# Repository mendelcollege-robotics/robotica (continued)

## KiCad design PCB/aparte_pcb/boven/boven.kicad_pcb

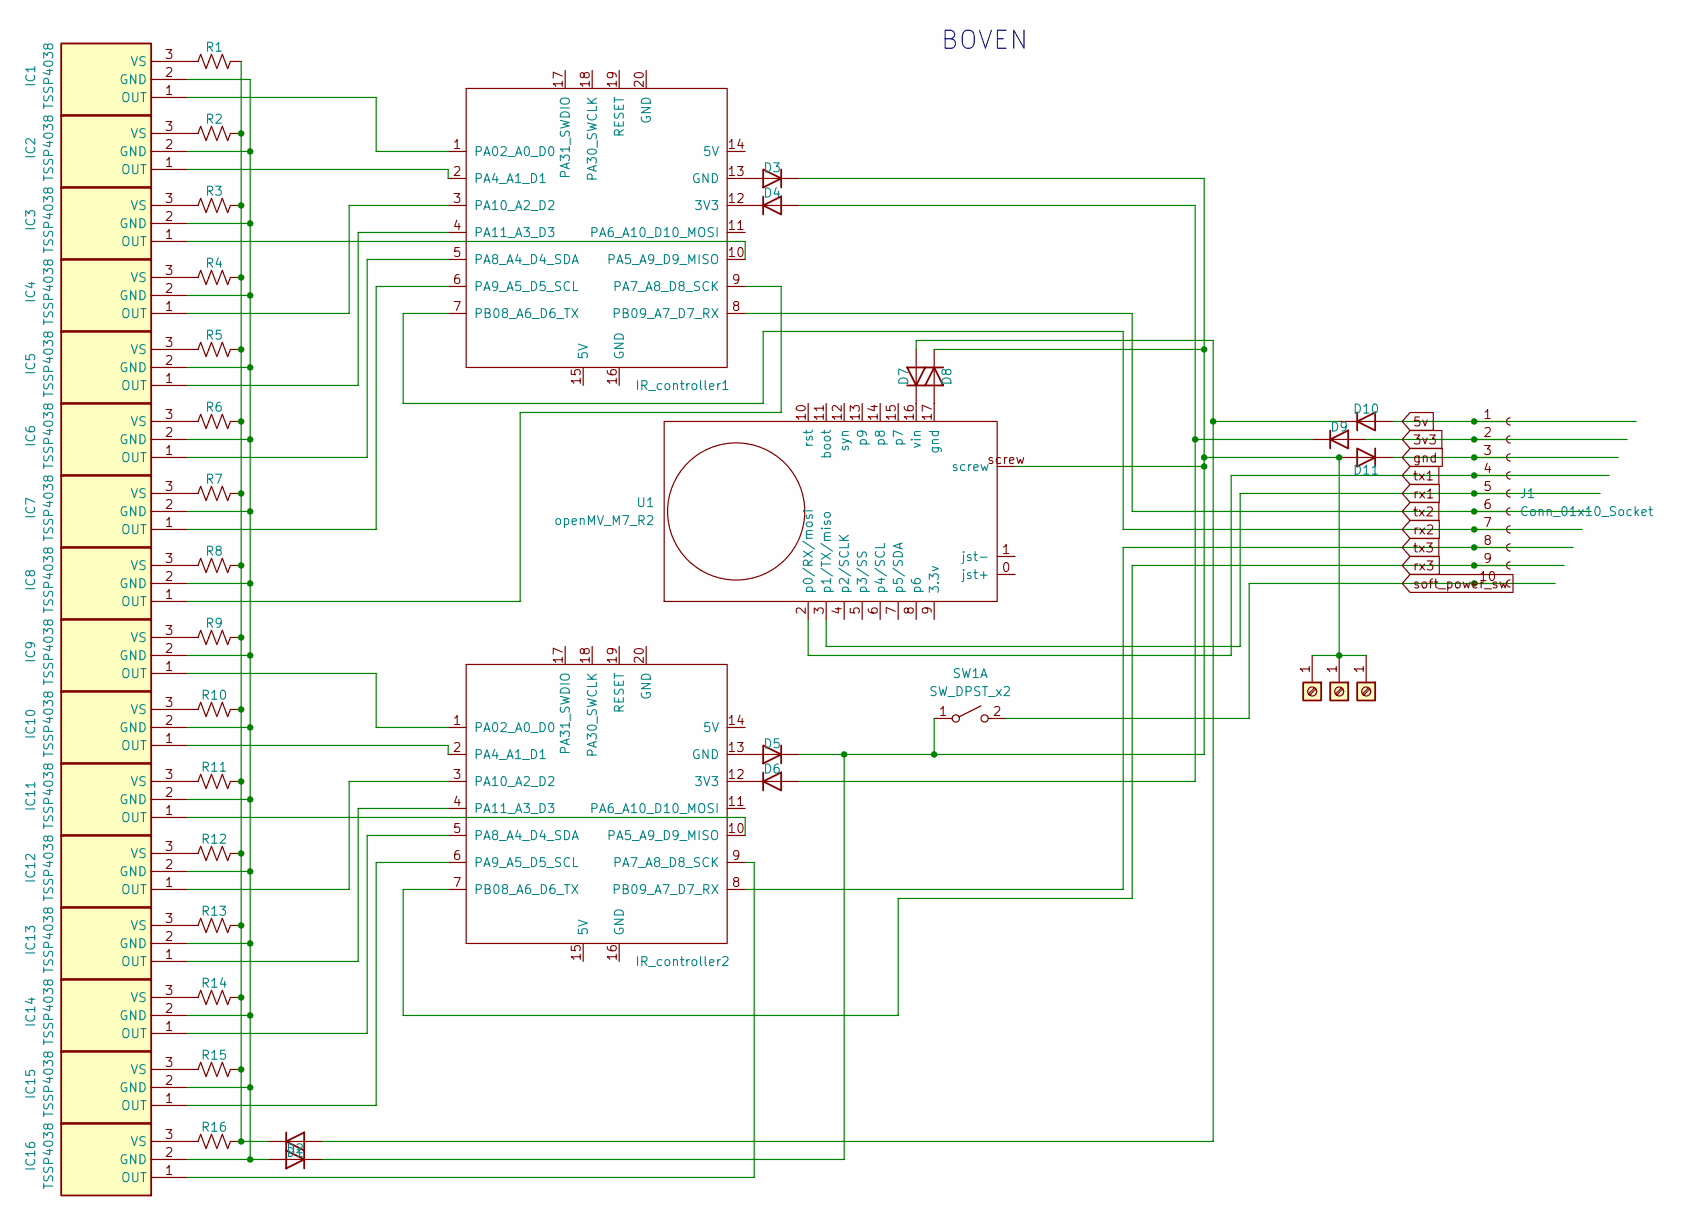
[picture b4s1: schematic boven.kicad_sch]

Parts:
D1, D2, D3, D4, D5, D6, D7, D8, D9, D10, D11: D; D_MELF-RM10_Universal_Handsoldering
IC1, IC2, IC3, IC4, IC5, IC6, IC7, IC8, IC9, IC10, IC11, IC12, IC13, IC14, IC15, IC16: TSSP4038; Manufacturer_Part_Number TSSP4038; Mouser Part Number 782-TSSP4038
IR_controller1, IR_controller2: Seeed Studio XIAO SAMD21; Seeduino Xiao Kicad af
J1: Conn_01x10_Socket; JST_EH_S10B-EH_1x10_P2.50mm_Horizontal
J2: Screw_Terminal_01x01; MountingHole_4.3mm_M4_DIN965_Pad
J3, J4: Screw_Terminal_01x01; MountingHole_4.3mm_M4_ISO7380_Pad
R1, R2, R3, R4, R5, R6, R7, R8, R9, R10, R11, R12, R13, R14, R15, R16: R_US; R_Axial_DIN0207_L6.3mm_D2.5mm_P10.16mm_Horizontal
SW1: SW_DPST_x2; R1966ABLKBLKEF
U1: openMV_M7_R2; openmv_m7_r2

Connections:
3v3: D9.2 (A), J1.2
5v: D10.2 (A), J1.1
unnamed: D1.2 (A), D7.2 (A), D10.1 (K)
unnamed: D1.1 (K), R1.2, R2.2, R3.2, R4.2, R5.2, R6.2, R7.2, R8.2, R9.2, R10.2, R11.2, R12.2, R13.2, R14.2, R15.2, R16.2
unnamed: D2.2 (A), IC1.2 (GND), IC2.2 (GND), IC3.2 (GND), IC4.2 (GND), IC5.2 (GND), IC6.2 (GND), IC7.2 (GND), IC8.2 (GND), IC9.2 (GND), IC10.2 (GND), IC11.2 (GND), IC12.2 (GND), IC13.2 (GND), IC14.2 (GND), IC15.2 (GND), IC16.2 (GND)
unnamed: D3.2 (A), IR_controller1.13 (GND)
unnamed: D4.2 (A), D6.2 (A), D9.1 (K)
unnamed: D4.1 (K), IR_controller1.12 (3V3)
unnamed: D5.2 (A), IR_controller2.13 (GND)
unnamed: D6.1 (K), IR_controller2.12 (3V3)
unnamed: D7.1 (K), U1.16 (vin)
unnamed: D8.2 (A), U1.17 (gnd)
unnamed: D2.1 (K), D3.1 (K), D5.1 (K), D8.1 (K), D11.2 (A), J2.1, J3.1, J4.1, SW1.1 (A), U1.screw
unnamed: IC1.1 (OUT), IR_controller1.1 (PA02_A0_D0)
unnamed: IC1.3 (VS), R1.1
unnamed: IC2.1 (OUT), IR_controller1.2 (PA4_A1_D1)
unnamed: IC2.3 (VS), R2.1
unnamed: IC3.1 (OUT), IR_controller1.10 (PA5_A9_D9_MISO)
unnamed: IC3.3 (VS), R3.1
unnamed: IC4.1 (OUT), IR_controller1.3 (PA10_A2_D2)
unnamed: IC4.3 (VS), R4.1
unnamed: IC5.1 (OUT), IR_controller1.4 (PA11_A3_D3)
unnamed: IC5.3 (VS), R5.1
unnamed: IC6.1 (OUT), IR_controller1.5 (PA8_A4_D4_SDA)
unnamed: IC6.3 (VS), R6.1
unnamed: IC7.1 (OUT), IR_controller1.6 (PA9_A5_D5_SCL)
unnamed: IC7.3 (VS), R7.1
unnamed: IC8.1 (OUT), IR_controller1.9 (PA7_A8_D8_SCK)
unnamed: IC8.3 (VS), R8.1
unnamed: IC9.1 (OUT), IR_controller2.1 (PA02_A0_D0)
unnamed: IC9.3 (VS), R9.1
unnamed: IC10.1 (OUT), IR_controller2.2 (PA4_A1_D1)
unnamed: IC10.3 (VS), R10.1
unnamed: IC11.1 (OUT), IR_controller2.10 (PA5_A9_D9_MISO)
unnamed: IC11.3 (VS), R11.1
unnamed: IC12.1 (OUT), IR_controller2.3 (PA10_A2_D2)
unnamed: IC12.3 (VS), R12.1
unnamed: IC13.1 (OUT), IR_controller2.4 (PA11_A3_D3)
unnamed: IC13.3 (VS), R13.1
unnamed: IC14.1 (OUT), IR_controller2.5 (PA8_A4_D4_SDA)
unnamed: IC14.3 (VS), R14.1
unnamed: IC15.1 (OUT), IR_controller2.6 (PA9_A5_D5_SCL)
unnamed: IC15.3 (VS), R15.1
unnamed: IC16.1 (OUT), IR_controller2.9 (PA7_A8_D8_SCK)
unnamed: IC16.3 (VS), R16.1
gnd: D11.1 (K), J1.3
rx1: J1.5, U1.3 (p1/TX/miso)
rx2: IR_controller1.7 (PB08_A6_D6_TX), J1.7
rx3: IR_controller2.7 (PB08_A6_D6_TX), J1.9
soft_power_sw: J1.10, SW1.2 (B)
tx1: J1.4, U1.2 (p0/RX/mosi)
tx2: IR_controller1.8 (PB09_A7_D7_RX), J1.6
tx3: IR_controller2.8 (PB09_A7_D7_RX), J1.8

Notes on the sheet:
BOVEN

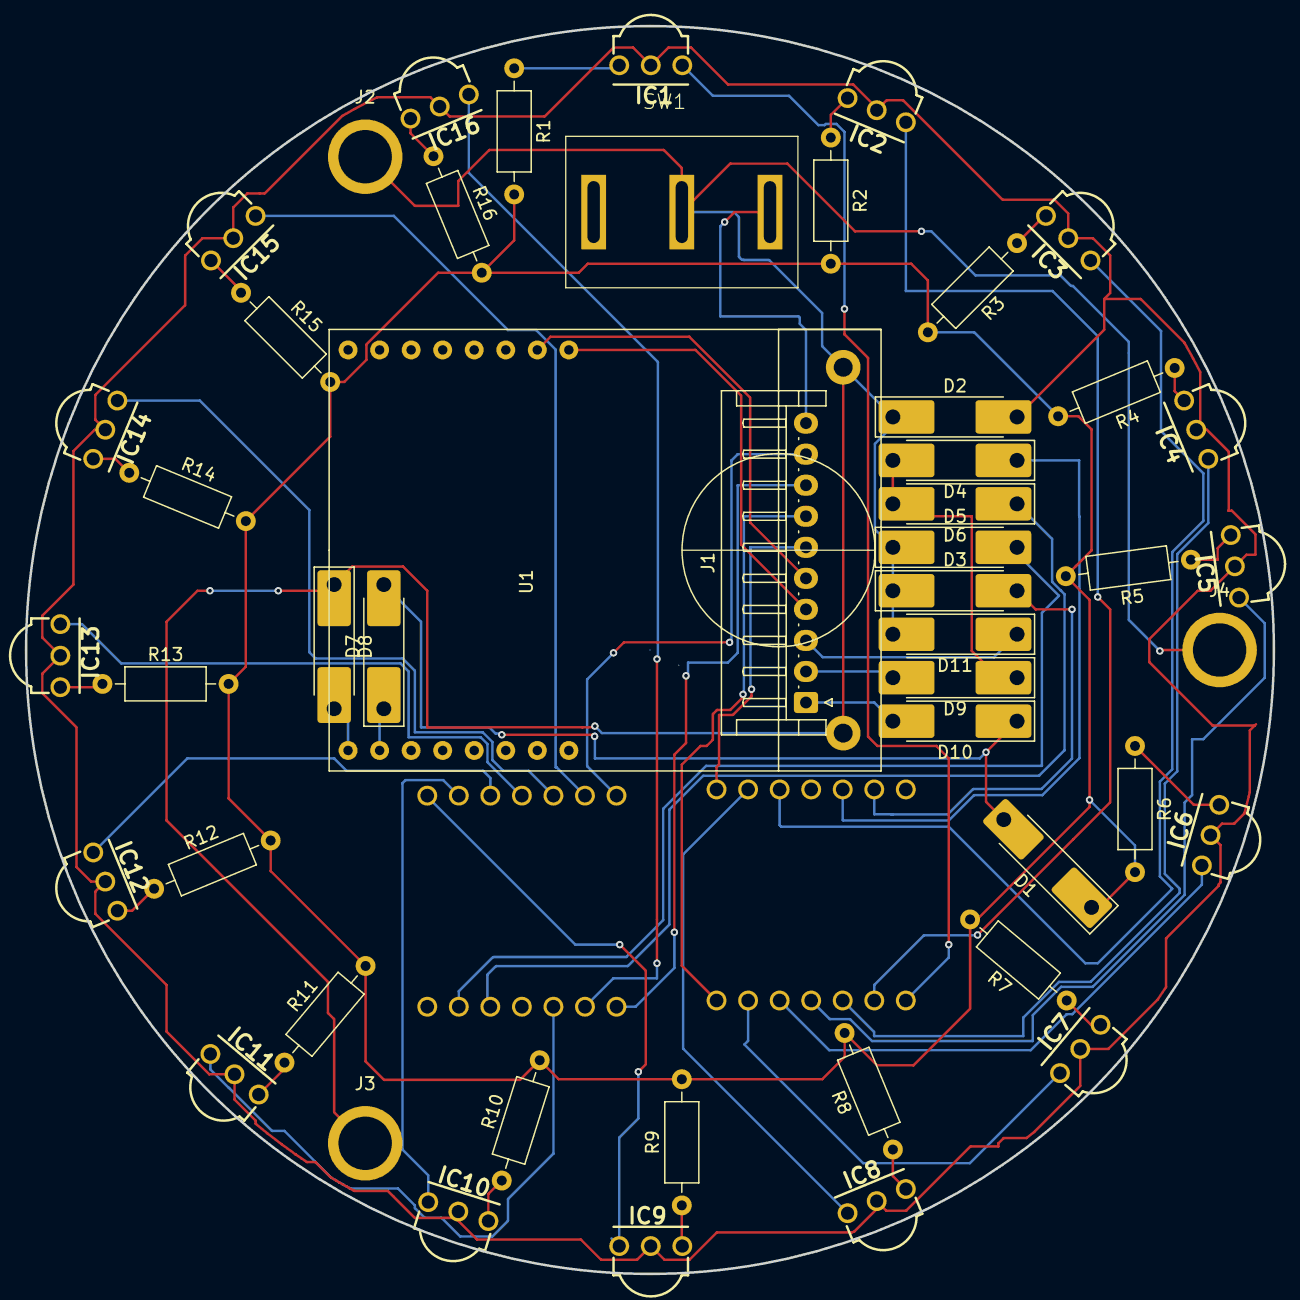
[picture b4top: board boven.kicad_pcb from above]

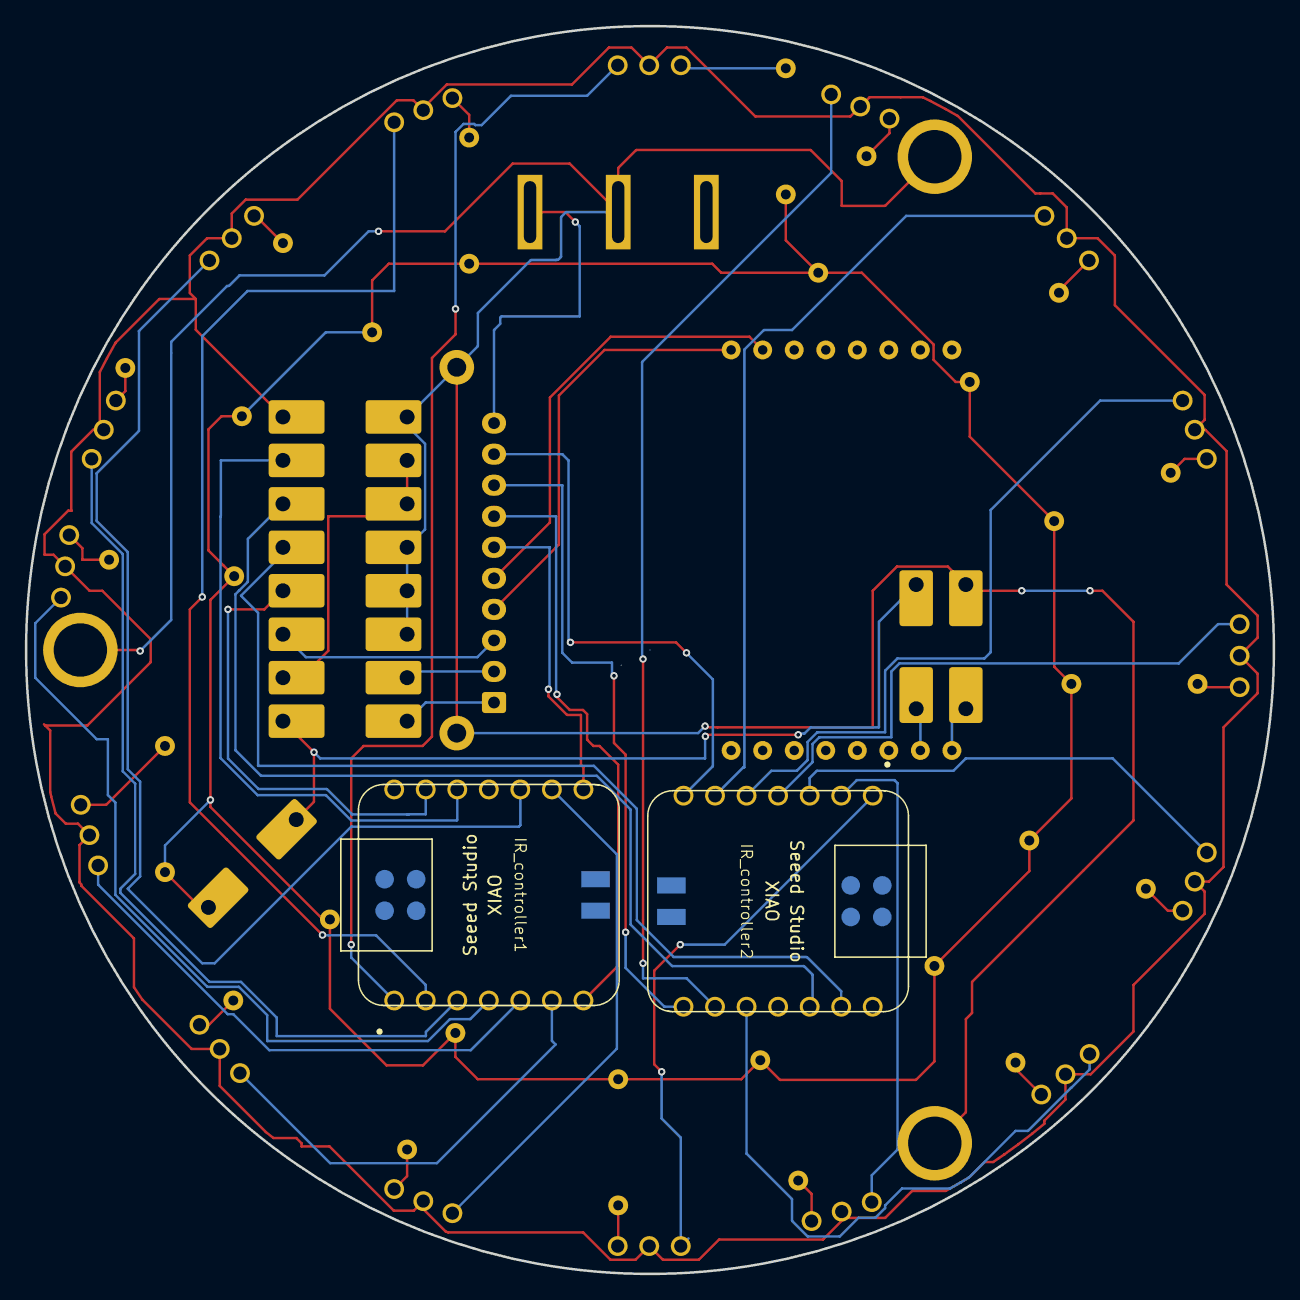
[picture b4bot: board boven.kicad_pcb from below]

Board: 2 copper layers, 100.5 x 100.5 mm, 51 parts (2 on the bottom side), 53 nets.

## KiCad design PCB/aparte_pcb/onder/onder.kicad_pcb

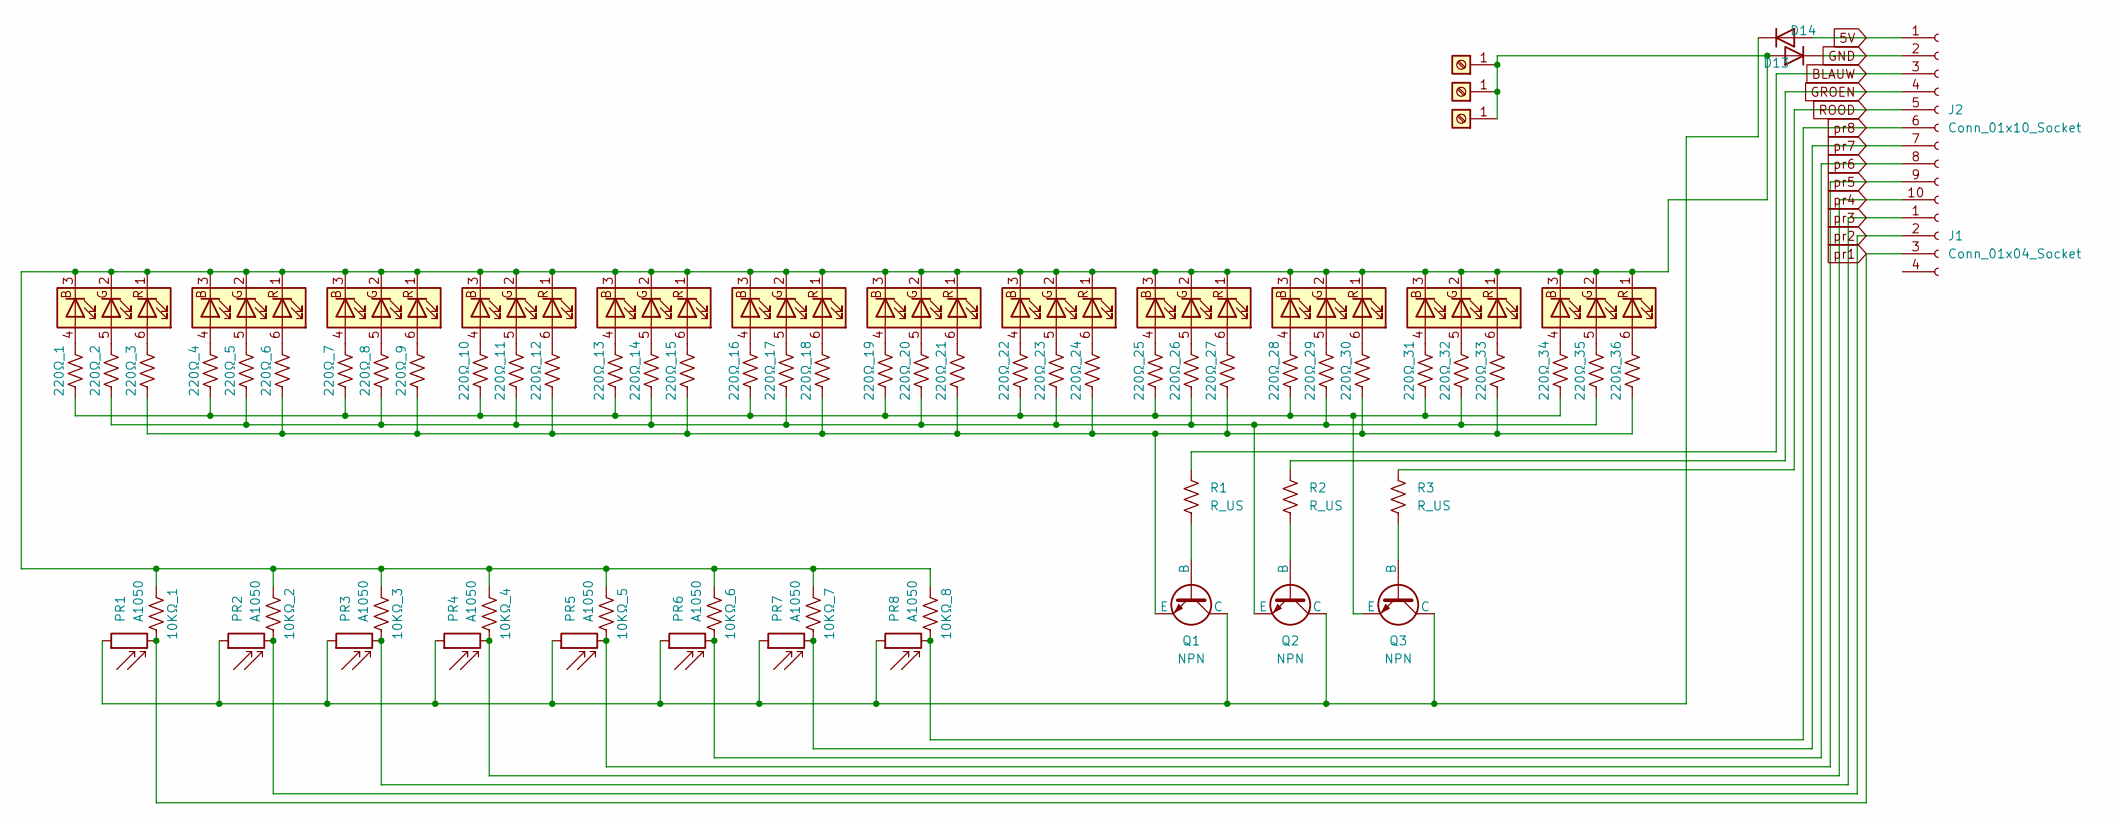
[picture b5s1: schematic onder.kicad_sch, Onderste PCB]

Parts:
10KΩ_1, 10KΩ_2, 10KΩ_3, 10KΩ_4, 10KΩ_5, 10KΩ_6, 10KΩ_7, 10KΩ_8, 220Ω_1, 220Ω_2, 220Ω_3, 220Ω_4, 220Ω_5, 220Ω_6, 220Ω_7, 220Ω_8, 220Ω_9, 220Ω_10, 220Ω_11, 220Ω_12, 220Ω_13, 220Ω_14, 220Ω_15, 220Ω_16, 220Ω_17, 220Ω_18, 220Ω_19, 220Ω_20, 220Ω_21, 220Ω_22, 220Ω_23, 220Ω_24, 220Ω_25, 220Ω_26, 220Ω_27, 220Ω_28, 220Ω_29, 220Ω_30, 220Ω_31, 220Ω_32, 220Ω_33, 220Ω_34, 220Ω_35, 220Ω_36: R_US; R_Axial_DIN0207_L6.3mm_D2.5mm_P10.16mm_Horizontal
D1, D2, D3, D4, D5, D6, D7, D8, D9, D10, D11, D12: LED_RGB; LED_RGB_5050-6
D13, D14: D; D_MELF-RM10_Universal_Handsoldering
J1: Conn_01x04_Socket; JST_EH_S4B-EH_1x04_P2.50mm_Horizontal
J2: Conn_01x10_Socket; JST_EH_S10B-EH_1x10_P2.50mm_Horizontal
J3, J4, J5: Screw_Terminal_01x01; MountingHole_4.3mm_M4_ISO7380_Pad
PR1, PR2, PR3, PR4, PR5, PR6, PR7, PR8: A1050; FOTORESist
Q1, Q2, Q3: NPN
R1, R2, R3: R_US; R_Axial_DIN0207_L6.3mm_D2.5mm_P10.16mm_Horizontal

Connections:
5V: D14.2 (A), J2.1
BLAUW: J2.3, R1.2
GND: D13.1 (K), J2.2
GROEN: J2.4, R2.2
unnamed: 220Ω_1.1, D1.4 (BA)
unnamed: 10KΩ_1.2, 10KΩ_2.2, 10KΩ_3.2, 10KΩ_4.2, 10KΩ_5.2, 10KΩ_6.2, 10KΩ_7.2, 10KΩ_8.2, D1.1 (RK), D1.2 (GK), D1.3 (BK), D2.1 (RK), D2.2 (GK), D2.3 (BK), D3.1 (RK), D3.2 (GK), D3.3 (BK), D4.1 (RK), D4.2 (GK), D4.3 (BK), D5.1 (RK), D5.2 (GK), D5.3 (BK), D6.1 (RK), D6.2 (GK), D6.3 (BK), D7.1 (RK), D7.2 (GK), D7.3 (BK), D8.1 (RK), D8.2 (GK), D8.3 (BK), D9.1 (RK), D9.2 (GK), D9.3 (BK), D10.1 (RK), D10.2 (GK), D10.3 (BK), D11.1 (RK), D11.2 (GK), D11.3 (BK), D12.1 (RK), D12.2 (GK), D12.3 (BK), D13.2 (A), J3.1, J4.1, J5.1
unnamed: 220Ω_2.1, D1.5 (GA)
unnamed: 220Ω_3.1, D1.6 (RA)
unnamed: 220Ω_4.1, D2.4 (BA)
unnamed: 220Ω_5.1, D2.5 (GA)
unnamed: 220Ω_6.1, D2.6 (RA)
unnamed: 220Ω_7.1, D3.4 (BA)
unnamed: 220Ω_8.1, D3.5 (GA)
unnamed: 220Ω_9.1, D3.6 (RA)
unnamed: 220Ω_10.1, D4.4 (BA)
unnamed: 220Ω_11.1, D4.5 (GA)
unnamed: 220Ω_12.1, D4.6 (RA)
unnamed: 220Ω_13.1, D5.4 (BA)
unnamed: 220Ω_14.1, D5.5 (GA)
unnamed: 220Ω_15.1, D5.6 (RA)
unnamed: 220Ω_16.1, D6.4 (BA)
unnamed: 220Ω_17.1, D6.5 (GA)
unnamed: 220Ω_18.1, D6.6 (RA)
unnamed: 220Ω_19.1, D7.4 (BA)
unnamed: 220Ω_20.1, D7.5 (GA)
unnamed: 220Ω_21.1, D7.6 (RA)
unnamed: 220Ω_22.1, D8.4 (BA)
unnamed: 220Ω_23.1, D8.5 (GA)
unnamed: 220Ω_24.1, D8.6 (RA)
unnamed: 220Ω_25.1, D9.4 (BA)
unnamed: 220Ω_26.1, D9.5 (GA)
unnamed: 220Ω_27.1, D9.6 (RA)
unnamed: 220Ω_28.1, D10.4 (BA)
unnamed: 220Ω_29.1, D10.5 (GA)
unnamed: 220Ω_30.1, D10.6 (RA)
unnamed: 220Ω_31.1, D11.4 (BA)
unnamed: 220Ω_32.1, D11.5 (GA)
unnamed: 220Ω_33.1, D11.6 (RA)
unnamed: 220Ω_34.1, D12.4 (BA)
unnamed: 220Ω_35.1, D12.5 (GA)
unnamed: 220Ω_36.1, D12.6 (RA)
unnamed: D14.1 (K), PR1.1, PR2.1, PR3.1, PR4.1, PR5.1, PR6.1, PR7.1, PR8.1, Q1.1 (C), Q2.1 (C), Q3.1 (C)
unnamed: Q1.2 (B), R1.1
unnamed: 220Ω_3.2, 220Ω_6.2, 220Ω_9.2, 220Ω_12.2, 220Ω_15.2, 220Ω_18.2, 220Ω_21.2, 220Ω_24.2, 220Ω_27.2, 220Ω_30.2, 220Ω_33.2, 220Ω_36.2, Q1.3 (E)
unnamed: Q2.2 (B), R2.1
unnamed: 220Ω_2.2, 220Ω_5.2, 220Ω_8.2, 220Ω_11.2, 220Ω_14.2, 220Ω_17.2, 220Ω_20.2, 220Ω_23.2, 220Ω_26.2, 220Ω_29.2, 220Ω_32.2, 220Ω_35.2, Q2.3 (E)
unnamed: Q3.2 (B), R3.1
unnamed: 220Ω_1.2, 220Ω_4.2, 220Ω_7.2, 220Ω_10.2, 220Ω_13.2, 220Ω_16.2, 220Ω_19.2, 220Ω_22.2, 220Ω_25.2, 220Ω_28.2, 220Ω_31.2, 220Ω_34.2, Q3.3 (E)
ROOD: J2.5, R3.2
pr1: 10KΩ_1.1, J1.3, PR1.2
pr2: 10KΩ_2.1, J1.2, PR2.2
pr3: 10KΩ_3.1, J1.1, PR3.2
pr4: 10KΩ_4.1, J2.10, PR4.2
pr5: 10KΩ_5.1, J2.9, PR5.2
pr6: 10KΩ_6.1, J2.8, PR6.2
pr7: 10KΩ_7.1, J2.7, PR7.2
pr8: 10KΩ_8.1, J2.6, PR8.2

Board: 2 copper layers, 77 parts (0 on the bottom side), 57 nets, no tracks yet.

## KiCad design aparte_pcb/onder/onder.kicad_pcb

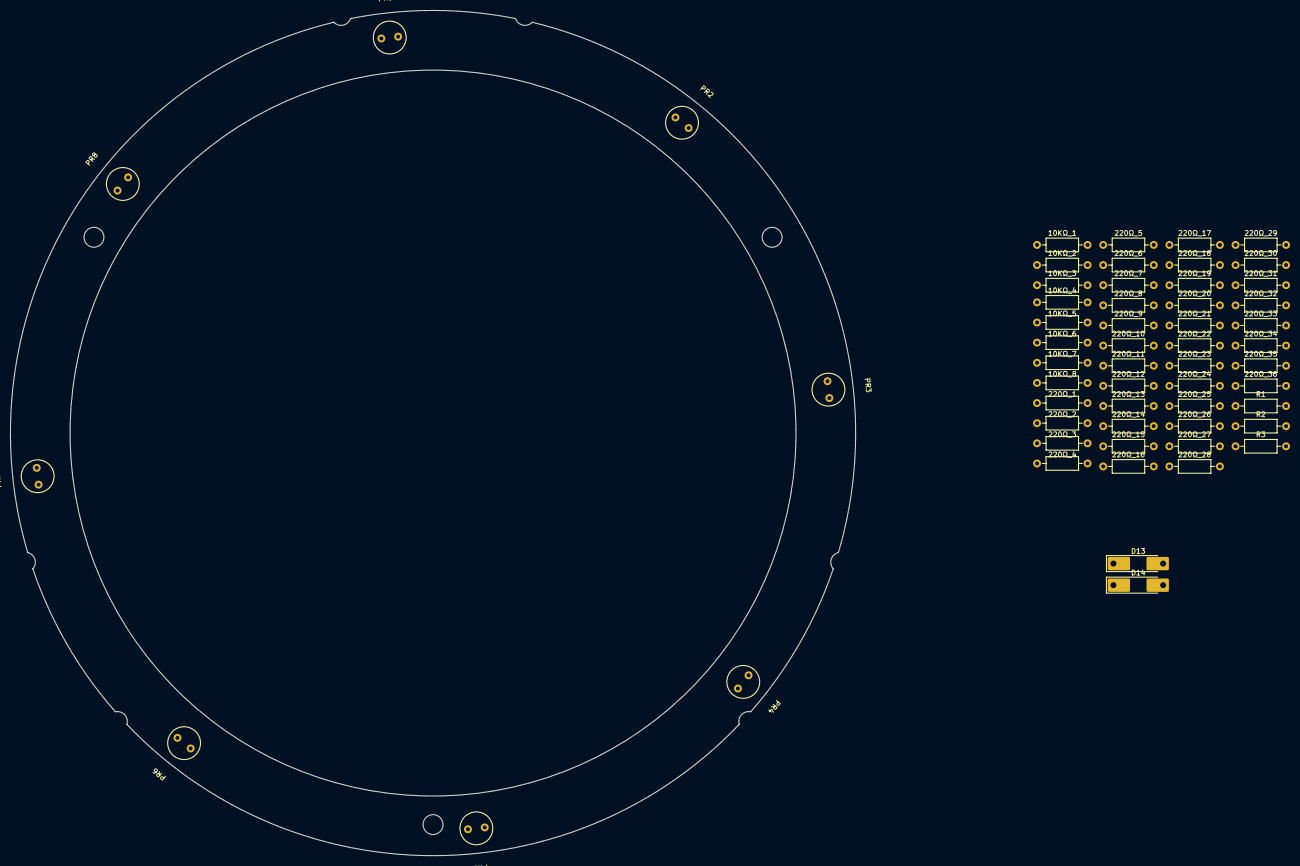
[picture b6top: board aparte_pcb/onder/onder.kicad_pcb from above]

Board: 2 copper layers, 170.0 x 170.0 mm, 57 parts (0 on the bottom side), 13 nets, no tracks yet.

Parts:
10KΩ_1, 10KΩ_2, 10KΩ_3, 10KΩ_4, 10KΩ_5, 10KΩ_6, 10KΩ_7, 10KΩ_8, 220Ω_1, 220Ω_2, 220Ω_3, 220Ω_4, 220Ω_5, 220Ω_6, 220Ω_7, 220Ω_8, 220Ω_9, 220Ω_10, 220Ω_11, 220Ω_12, 220Ω_13, 220Ω_14, 220Ω_15, 220Ω_16, 220Ω_17, 220Ω_18, 220Ω_19, 220Ω_20, 220Ω_21, 220Ω_22, 220Ω_23, 220Ω_24, 220Ω_25, 220Ω_26, 220Ω_27, 220Ω_28, 220Ω_29, 220Ω_30, 220Ω_31, 220Ω_32, 220Ω_33, 220Ω_34, 220Ω_35, 220Ω_36: R_US; R_Axial_DIN0207_L6.3mm_D2.5mm_P10.16mm_Horizontal
D13, D14: D; D_MELF-RM10_Universal_Handsoldering
PR1, PR2, PR3, PR4, PR5, PR6, PR7, PR8: A1050; FOTORES
R1, R2, R3: R_US; R_Axial_DIN0207_L6.3mm_D2.5mm_P10.16mm_Horizontal

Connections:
unnamed: 10KΩ_1.2, 10KΩ_2.2, 10KΩ_3.2, 10KΩ_4.2, 10KΩ_5.2, 10KΩ_6.2, 10KΩ_7.2, 10KΩ_8.2, D13.2 (A)
unnamed: D14.1 (K), PR1.1, PR2.1, PR3.1, PR4.1, PR5.1, PR6.1, PR7.1, PR8.1
unnamed: 220Ω_3.2, 220Ω_6.2, 220Ω_9.2, 220Ω_12.2, 220Ω_15.2, 220Ω_18.2, 220Ω_21.2, 220Ω_24.2, 220Ω_27.2, 220Ω_30.2, 220Ω_33.2, 220Ω_36.2
unnamed: 220Ω_2.2, 220Ω_5.2, 220Ω_8.2, 220Ω_11.2, 220Ω_14.2, 220Ω_17.2, 220Ω_20.2, 220Ω_23.2, 220Ω_26.2, 220Ω_29.2, 220Ω_32.2, 220Ω_35.2
unnamed: 220Ω_1.2, 220Ω_4.2, 220Ω_7.2, 220Ω_10.2, 220Ω_13.2, 220Ω_16.2, 220Ω_19.2, 220Ω_22.2, 220Ω_25.2, 220Ω_28.2, 220Ω_31.2, 220Ω_34.2
pr1: 10KΩ_1.1, PR1.2
pr2: 10KΩ_2.1, PR2.2
pr3: 10KΩ_3.1, PR3.2
pr4: 10KΩ_4.1, PR4.2
pr5: 10KΩ_5.1, PR5.2
pr6: 10KΩ_6.1, PR6.2
pr7: 10KΩ_7.1, PR7.2
pr8: 10KΩ_8.1, PR8.2

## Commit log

2022-12-08 full half or no
2022-12-08 fouths
2022-12-08 eights
2022-12-08 Update LICENSE
2022-12-08 didvthing
2024-04-29 add buz
2024-04-29 buzz debug
2024-04-30 Create l
2024-04-30 Update and rename pcb/l to pcb_readme
2024-05-03 Commit message
2024-05-04 pcb boven gemaakt
2024-05-04 pcb onder gemaakt
2024-06-02 add files
2024-06-03 add connect between teensy and openmv
2024-06-03 update com
2024-06-05 add mcp
2024-06-05 add mcu
2024-06-09 Create e
2024-06-09 upd pcb
2024-06-09 manifacture
2024-06-09 pcb_onder y
2024-06-10 add CODE
2024-06-10 code
2024-06-11 3d file pcb
2024-06-11 lower_pcb
2024-06-12 add_3d
2024-06-14 dfas
2024-06-15 4dip
2024-06-20 poster
2024-06-20 dsfa
2024-06-21 post
2024-06-21 poster readme weird fix
2024-06-22 update repo structure update poster add code flowchart
2024-06-22 remove OLD update poster
2024-06-23 git structure change poster
2024-06-24 lower pcb
2024-06-25 3d file of pcb
2024-06-26 part diagram
2024-06-30 motor drivers
2024-06-30 to fix: change mcp2.analogWrite(m1pwm1, spdA); to us softPWM
2024-07-03 soft PWM added
2024-07-03 direction code and better IR seeker code
2024-07-06 Motor Calibration capabilities
2024-07-07 Motor driver code complette need to test/fix MCP23017
2024-07-07 setting 1 complete need to do 2, 3, 4
2024-07-16 maini code
2024-07-22 change folder struct
2024-07-27 PCB schemas
2024-08-27 add full pcb schema
2024-09-05 nog lang niet klaar.
2024-09-05 update pcb led
2024-10-06 dfgs
2024-10-07 Onder pcb kan gemaakt worden
    De rest moet nog uitgewerkt worden
2024-10-07 Onder pcb kan gemaakt worden
2024-10-08 ONDERPCB
2024-10-08 UPDATE FOLDER STUCTURE
    MOET APARTE_PCB NOG VERWIJDERTEN WINDOWS HEEFT BEST VERGRENDELD
2024-10-13 Rename 3dfiles/Robotica Volledige Robot3 v5.f3z to 3dfiles/backups/Robotica Volledige Robot3 v5.f3z
2024-10-14 laaste boutjes
2024-10-14 Rename 3dfiles/Robotica Volledige Robot3 v11.f3z to 3dfiles/backups/Robotica Volledige Robot3 v11.f3z
2024-10-14 kleine aanpassing op vorige aanpassingen
2024-10-14 Rename 3dfiles/Robotica Volledige Robot3 v13.f3z to 3dfiles/backups/Robotica Volledige Robot3 v13.f3z
2024-10-17 pcb's
2024-10-18 midden bijna klaar
2024-10-18 alleen solinoid nog
2024-10-19 solenoid gaten
2024-10-19 Rename 3dfiles/Robotica Volledige Robot3 v15.f3z to 3dfiles/backups/Robotica Volledige Robot3 v15.f3z
2024-10-19 Rename 3dfiles/Robotica Volledige Robot3 v15.stl to 3dfiles/backups/Robotica Volledige Robot3 v15.stl
2024-10-19 kicker
2024-10-30 Create Onder pcb bijna af
2024-10-30 asedfdgasfsdgfvdfgasdfgbs
2024-11-01 schroef geaard
    moet nog onderste schroef
2024-11-04 Rename 3dfiles/Robotica Volledige Robot3 v16.f3z to 3dfiles/backups/Robotica Volledige Robot3 v16.f3z
2024-11-04 Rename 3dfiles/Robotica Volledige Robot3 v16.stl to 3dfiles/backups/Robotica Volledige Robot3 v16.stl
2024-11-04 Rename 3dfiles/Robotica Volledige Robot3 v17.f3z to 3dfiles/backups/Robotica Volledige Robot3 v17.f3z
2024-11-04 Rename 3dfiles/Robotica Volledige Robot3 v17.stl to 3dfiles/backups/Robotica Volledige Robot3 v17.stl
2024-11-06 pcb pre autoroute upload
2024-11-06 Onderste mesh veranderd
2024-11-06 Rename 3dfiles/Robotica Volledige Robot3 v18.f3z to 3dfiles/backups/Robotica Volledige Robot3 v18.f3z
2024-11-06 Rename 3dfiles/Robotica Volledige Robot3 v18.stl to 3dfiles/backups/Robotica Volledige Robot3 v18.stl
2024-11-07 7-11
2024-11-07 af ready to check
2024-11-08 dgsrf
2024-12-19 Create verbeterde code door chatgpt
    ik heb de code in chat gestopt en heeft mij dit terug geschreven, kunnen we hier iets mee?
2025-02-06 halloi test
2025-03-20 things
2025-03-20 EEASFEESDFASDF
2025-03-20 send messages via serial
2025-03-20 able to convert ir signal into degrees
2025-03-20 issue 15 should be fixed
2025-03-20 color
2025-03-20 PWM with motors
2025-03-20 test
2025-03-21 fix serial
2025-03-21 fix PWM
2025-03-23 updated repo structure
2025-03-23 softpwm
2025-03-23 serial
2025-03-24 added git ignore files and removed .lck files
2025-03-26 Rename 3dfiles/soccerfield.obj to 3dfiles/oud/soccerfield.obj
2025-03-26 Rename 3dfiles/PCBboven.3mf to 3dfiles/oud/PCBboven.3mf
2025-03-26 Rename 3dfiles/PCBmidden.stl to 3dfiles/oud/PCBmidden.stl
2025-03-26 Rename 3dfiles/PCBonder.3mf to 3dfiles/oud/PCBonder.3mf
2025-03-26 Rename 3dfiles/PCBondermesh.3mf to 3dfiles/oud/PCBondermesh.3mf
2025-03-26 Rename 3dfiles/PCBondermesh.stl to 3dfiles/oud/PCBondermesh.stl
2025-03-26 Rename 3dfiles/feld.20240723-125216.FCBak to 3dfiles/oud/feld.20240723-125216.FCBak
2025-03-26 Rename 3dfiles/feld.FCStd to 3dfiles/oud/feld.FCStd
2025-03-26 Rename 3dfiles/onderpcb(new).dxf to 3dfiles/oud/onderpcb(new).dxf
2025-03-26 Rename 3dfiles/pcb_onder(oud).dxf to 3dfiles/oud/pcb_onder(oud).dxf
2025-03-26 Rename 3dfiles/pcb_midden(onderste_face).dxf to 3dfiles/oud/pcb_midden(onderste_face).dxf
2025-03-26 Rename 3dfiles/pcb_midden(bovenste_face).dxf to 3dfiles/oud/pcb_midden(bovenste_face).dxf
2025-03-26 Rename 3dfiles/pcb_boven.dxf to 3dfiles/oud/pcb_boven.dxf
2025-03-26 Rename 3dfiles/Robot V3.1 concept v3.f3z to 3dfiles/oud/Robot V3.1 concept v3.f3z
2025-03-26 Rename 3dfiles/Robotica Volledige Robot3 v29.f3z to 3dfiles/oud/Robotica Volledige Robot3 v29.f3z
2025-03-26 Rename 3dfiles/Robotica Volledige Robot3 v29.stl to 3dfiles/oud/Robotica Volledige Robot3 v29.stl
2025-03-27 oude shit
2025-04-01 did a lot of thing lately
2025-04-06 nuttige bronnen om te leren
2025-04-06 test sign key
    Multi-line description of commit,
    feel free to be detailed.
2025-04-06 foto robot (poster?)
2025-04-24 sim for omni drive
2025-05-07 ksdbks
2025-05-08 test sign live usb
2025-05-08 paar best vergeten
2025-05-11 added encoder again
    Multi-line description of commit,
    feel free to be detailed.
2025-05-12 cam comm + readme -4
    Multi-line description of commit,
    feel free to be detailed.
2025-05-22 create issue templates
2025-11-14 INITIAL commit
    mosrtly the bottom pcb
2025-11-14 test
    test
2025-11-14 begin pcb total
2025-11-15 power toegevoegd
2025-11-15 V1.01
2025-11-17 pcb changes
    -file now in electronics
    -motordriver integraded
    -etc
2025-11-20 -motor driver -imu !!!need to check logic level converters!!!
2025-11-20 pinnen toegevoegd en goede eps32
2025-11-20 begin boven PCB
2025-11-20 boven pcb best ver af
2025-11-20 alleen nog cxampera
2025-11-21 some final adjustments.
2025-11-21 boven pcb af
2025-11-21 M1 is af
2025-11-21 fsdgal;nk
2025-11-28 V1.1
2025-12-02 motor driver symbol changed
2026-02-08 SOFTPWM
    Multi-line description of commit,
    feel free to be detailed.
    [Issue: X]
2026-02-08 debug message)
    Multi-line description of commit,
    feel free to be detailed.
    [Issue: X]
2026-02-08 created PID and it better fucking works
    Multi-line description of commit,
    feel free to be detailed.
    [Issue: X]
2026-02-08 im a idiot
    had m1encSP to < 0 give error but a motor can also be not moving no < 0 so
2026-02-08 i am the only one who reads there anyways so why do i bother
    imagen there is a butifull commit message here
    _____________________________________
    / Nothing so needs reforming as other \
    | people's habits. |
    | |
    \ -- Mark Twain /
2026-02-08 why does github say unverified
    added single empy line
    [Issue: X]
2026-02-08 im bored
    _____________________________
    < Avoid reality at all costs. >
    -----------------------------
    \
    \
    /\_)o<
